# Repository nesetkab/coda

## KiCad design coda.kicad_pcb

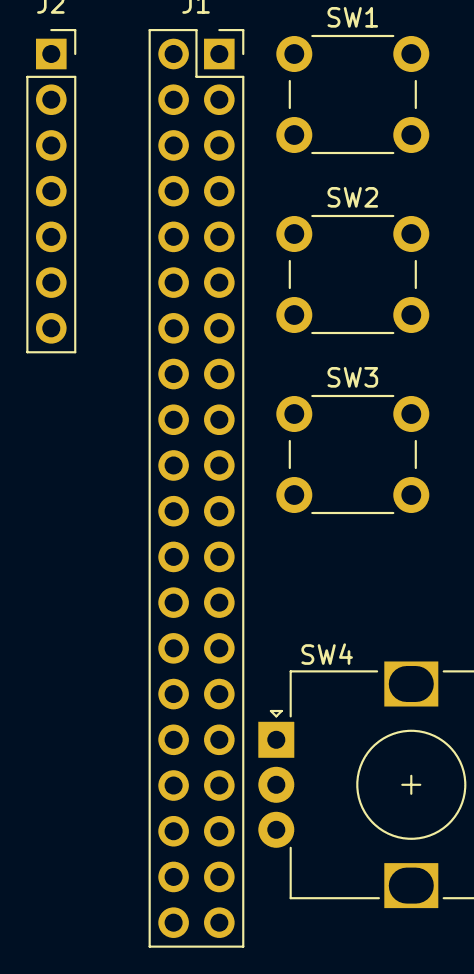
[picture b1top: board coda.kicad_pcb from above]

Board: 2 copper layers, 6 parts (0 on the bottom side), 11 nets, no tracks yet.

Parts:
J1: Conn_02x20_Odd_Even; PinSocket_2x20_P2.54mm_Vertical
J2: Conn_01x07; PinSocket_1x07_P2.54mm_Vertical
SW1, SW2, SW3: SW_Push; SW_PUSH_6mm_H5mm
SW4: RotaryEncoder_Switch; RotaryEncoder_Alps_EC12E_Vertical_H20mm

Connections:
GND: J2.6, SW1.1, SW2.1, SW3.1
unnamed: J1.4, J2.7
unnamed: J1.7, SW4.B
unnamed: J1.9, SW4.C
unnamed: J1.11, SW4.A
unnamed: J1.12, J2.2
unnamed: J1.15, SW1.2
unnamed: J1.16, SW3.2
unnamed: J1.18, SW2.2
unnamed: J1.35, J2.1
unnamed: J1.40, J2.3
